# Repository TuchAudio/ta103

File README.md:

# TuchAudio 103
Discrete, simple op-amp phono preamp

## Purpose
The most simple discrete op-amp, with **just 4 transistors** per channel -- a _3-transistor_ design was tried, but performed poorly.

## Design quirks

An op-amp this simple doesn't have too much of _open-loop gain_, thus the approximate formulae usually used are **no longer valid**. For this reason, _bass performance_ is just acceptable (but within _DIN 45.500_ specs).

DIN and RCA jacks are provided for signal input. Since the _native_ input impedance is around **110 kΩ**, space for suitable load (`Rx` and `Cx`) is provided for perfect adaptation; but for added flexibility, it is possible to use the free input for a suitable RC combo in parallel, to match the appropriate cartridge load.

Originally intended to be connected thru the [501 Input Selector board](../../../ta501), both output pins and power input are at compatible locations within each board. An aditional RCA **output** jack can be installed in order to use the circuit as a _stand-alone preamp_.

The use of an _asymmetric_ power supply (and its associated feedback _DC-blocking capacitor_) means that **it takes a few seconds** for the preamp to operate after powerup (or a noticeable supply voltage change).

### Stability

As any other amplifier with _asymmetrical power supply_, the PSRR is very poor, thus a **well filtered, stable** power supply is essential. Increasing (within reason) `R115/R215` may help a bit.

### Suggested mods

#### Standalone mode

Despite being designed around a 12 Volt power supply, this can be run from a single **9 Volt battery**, with minor changes and similar performance.

- `R115/R215`: use **220 Ω** instead of 330.
- `R103/R110/R203/R210`: use **8.2 kΩ** instead of 12K.

#### IEC1976/Neumann ammendments

The stated values are designed around these _ammendments_ to the **RIAA curve**; but since they're currently _deprecated_, you may get **improved bass response** by turning back to RIAA correction:

- `C104/C204`: do not mount (Neumann ammendment)
- `C106/C206`: use **470 nF** or more instead of 100 nF (which made a _-3 dB point at 20 Hz_ **over 108 kΩ** of the input on the _original design_ of the 501 board)

## Specs

_Measured thru a **501 input board** (tape rec. output), 12 V supply_

- **Power supply:** 9-12 V, asymmetrical, max. 6 mA
- **Input connectors:** 2x RCA plus DIN (in parallel)
- **Gain at 1 kHz:** 47x (+33.45 dB)
- **Input sensitivity:** 3.8 mV (for 180 mV output)
- **Input impedance:** 110 kΩ; adjusted by `Rx/Cx`, either internal or external.
- **Output level and impedance:** 180 mV / 3.3 KΩ
- **Overload margin:** at least +15 dB
- **Signal-to-noise ratio:** TBD
- **Frequency response:** 40 Hz - 20 kHz _(+0.25/-3 dB deviation from RIAA)_
- **Distortion:**

| Harmonic | nominal output | +15 dB overload |
| -------- | -------------- | --------------- |
| 2nd      | negligible     | 0.5 %           |
| 3rd      | 0.1 %          | 0.9 %           |
| 4th      | 0.11 %         | 0.3 %           |

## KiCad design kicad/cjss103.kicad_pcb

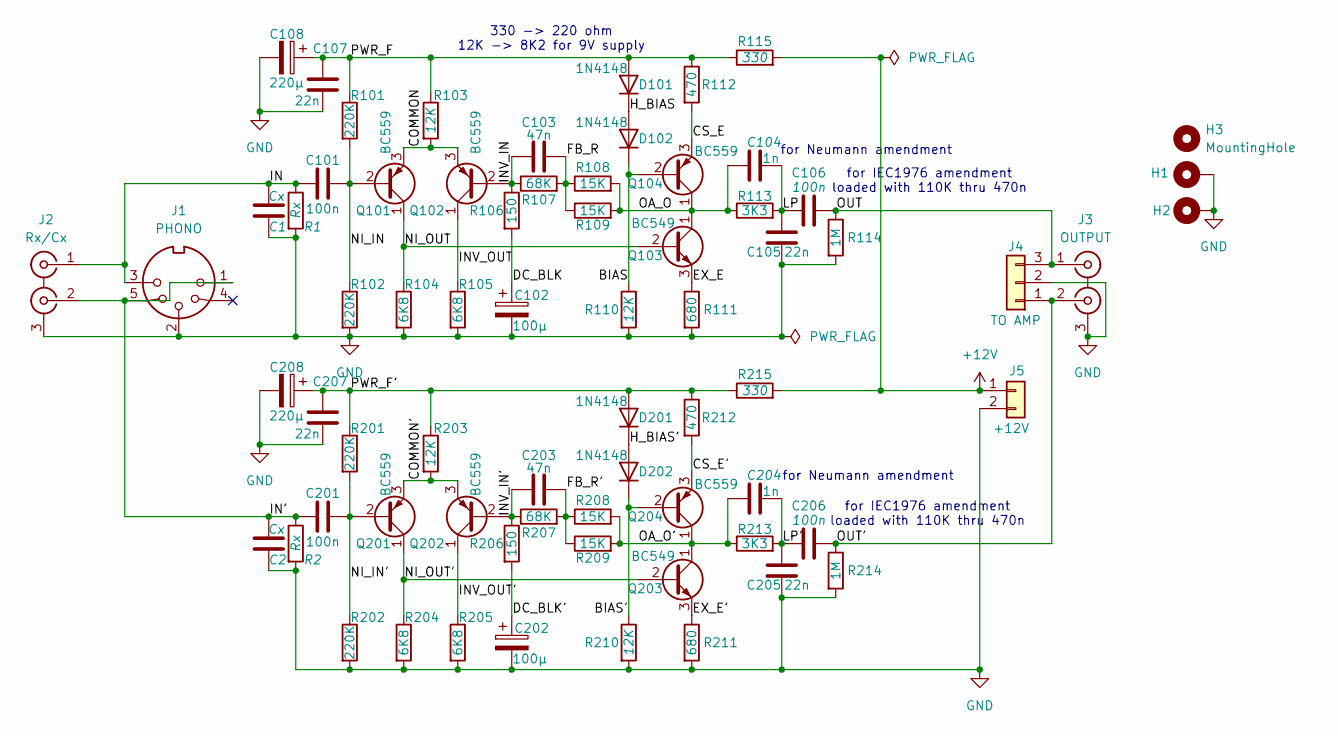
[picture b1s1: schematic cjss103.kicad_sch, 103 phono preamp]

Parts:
C1, C2: Cx; PinSocket_1x02_P2.54mm_Vertical
C101, C106, C201, C206: 100n; C_Rect_L7.2mm_W2.5mm_P5.00mm_FKS2_FKP2_MKS2_MKP2
C102, C202: 100µ; CP_Radial_D4.0mm_P1.50mm
C103, C203: 47n; C_Rect_L11.5mm_W2.0mm_P10.00mm_MKT
C104, C204: 1n; C_Rect_L7.2mm_W2.5mm_P5.00mm_FKS2_FKP2_MKS2_MKP2
C105, C205: 22n; C_Rect_L7.2mm_W2.5mm_P5.00mm_FKS2_FKP2_MKS2_MKP2
C107, C207: 22n; C_Disc_D6.0mm_W2.5mm_P5.00mm
C108, C208: 220µ; CP_Radial_D6.3mm_P2.50mm
D101, D102, D201, D202: 1N4148; D_DO-35_SOD27_P7.62mm_Horizontal
H1, H2: MountingHole_Pad; MountingHole_3.2mm_M3_DIN965_Pad
H3: MountingHole; MountingHole_3.2mm_M3
J1: PHONO; DIN 5-180deg
J2: Rx/Cx; 2xRCA_vertical
J3: OUTPUT; 2xRCA_vertical
J4: TO AMP; PinHeader_1x03_P2.54mm_Horizontal
J5: +12V; PinHeader_1x02_P2.54mm_Horizontal
Q101, Q102, Q104, Q201, Q202, Q204: BC559; TO-92_Inline
Q103, Q203: BC549; TO-92_Inline
R1, R2: Rx; PinSocket_1x02_P2.54mm_Vertical
R101, R102, R201, R202: 220K; R_Axial_DIN0207_L6.3mm_D2.5mm_P10.16mm_Horizontal
R103, R110, R203, R210: 12K; R_Axial_DIN0207_L6.3mm_D2.5mm_P10.16mm_Horizontal
R104, R105, R204, R205: 6K8; R_Axial_DIN0207_L6.3mm_D2.5mm_P10.16mm_Horizontal
R106, R206: 150; R_Axial_DIN0207_L6.3mm_D2.5mm_P10.16mm_Horizontal
R107, R207: 68K; R_Axial_DIN0207_L6.3mm_D2.5mm_P10.16mm_Horizontal
R108, R109, R208, R209: 15K; R_Axial_DIN0207_L6.3mm_D2.5mm_P10.16mm_Horizontal
R111, R211: 680; R_Axial_DIN0207_L6.3mm_D2.5mm_P10.16mm_Horizontal
R112, R212: 470; R_Axial_DIN0207_L6.3mm_D2.5mm_P10.16mm_Horizontal
R113, R213: 3K3; R_Axial_DIN0207_L6.3mm_D2.5mm_P10.16mm_Horizontal
R114, R214: 1M; R_Axial_DIN0207_L6.3mm_D2.5mm_P10.16mm_Horizontal
R115, R215: 330; R_Axial_DIN0207_L6.3mm_D2.5mm_P10.16mm_Horizontal

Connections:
+12V: J5.1, R115.2, R215.2
/BIAS: D102.1 (K), Q104.2 (B), R110.1
/BIAS': D202.1 (K), Q204.2 (B), R210.1
/COMMON: Q101.3 (E), Q102.3 (E), R103.2
/COMMON': Q201.3 (E), Q202.3 (E), R203.2
/CS_E: Q104.3 (E), R112.2
/CS_E': Q204.3 (E), R212.2
/DC_BLK: C102.1, R106.2
/DC_BLK': C202.1, R206.2
/EX_E: Q103.3 (E), R111.1
/EX_E': Q203.3 (E), R211.1
/FB_R: C103.2, R107.2, R108.1, R109.1
/FB_R': C203.2, R207.2, R208.1, R209.1
/H_BIAS: D101.1 (K), D102.2 (A)
/H_BIAS': D201.1 (K), D202.2 (A)
/IN: C1.1, C101.1, J1.3, J2.1 (IN1), R1.1
/IN': C2.1, C201.1, J1.1, J1.5, J2.2 (IN2), R2.1
/INV_IN: C103.1, Q102.2 (B), R106.1, R107.1
/INV_IN': C203.1, Q202.2 (B), R206.1, R207.1
/INV_OUT: Q102.1 (C), R105.1
/INV_OUT': Q202.1 (C), R205.1
/LP: C104.2, C105.2, C106.1, R113.2
/LP': C204.2, C205.2, C206.1, R213.2
/NI_IN: C101.2, Q101.2 (B), R101.2, R102.1
/NI_IN': C201.2, Q201.2 (B), R201.2, R202.1
/NI_OUT: Q101.1 (C), Q103.2 (B), R104.1
/NI_OUT': Q201.1 (C), Q203.2 (B), R204.1
/OA_O: C104.1, Q103.1 (C), Q104.1 (C), R108.2, R109.2, R113.1
/OA_O': C204.1, Q203.1 (C), Q204.1 (C), R208.2, R209.2, R213.1
/OUT: C106.2, J3.1 (IN1), J4.3, R114.1
/OUT': C206.2, J3.2 (IN2), J4.1, R214.1
/PWR_F: C107.2, C108.1, D101.2 (A), R101.1, R103.1, R112.1, R115.1
/PWR_F': C207.2, C208.1, D201.2 (A), R201.1, R203.1, R212.1, R215.1
GND: C1.2, C2.2, C102.2, C105.1, C107.1, C108.2, C202.2, C205.1, C207.1, C208.2, H1.1, H2.1, J1.2, J2.3 (EXT), J3.3 (EXT), J4.2, J5.2, R1.2, R2.2, R102.2, R104.2, R105.2, R110.2, R111.2, R114.2, R202.2, R204.2, R205.2, R210.2, R211.2, R214.2

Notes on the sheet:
for Neumann amendment
for IEC1976 amendment loaded with 110K thru 470n
330 -> 220 ohm 12K -> 8K2 for 9V supply

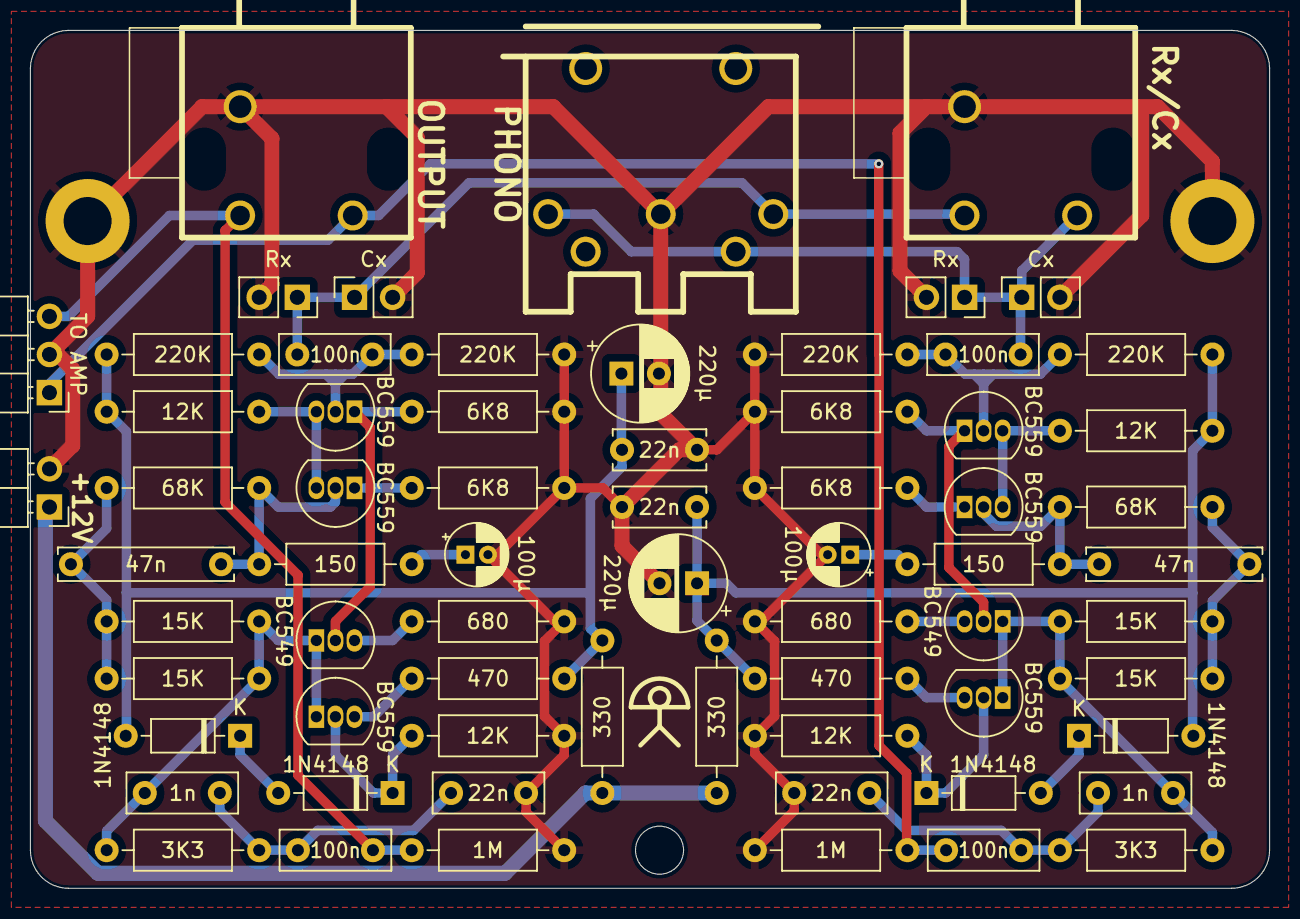
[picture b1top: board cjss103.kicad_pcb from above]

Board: 2 copper layers, 82.6 x 57.2 mm, 70 parts (0 on the bottom side), 34 nets.

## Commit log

2025-11-08 add KiCAD files
2025-11-12 add pictures
2025-11-24 add links
